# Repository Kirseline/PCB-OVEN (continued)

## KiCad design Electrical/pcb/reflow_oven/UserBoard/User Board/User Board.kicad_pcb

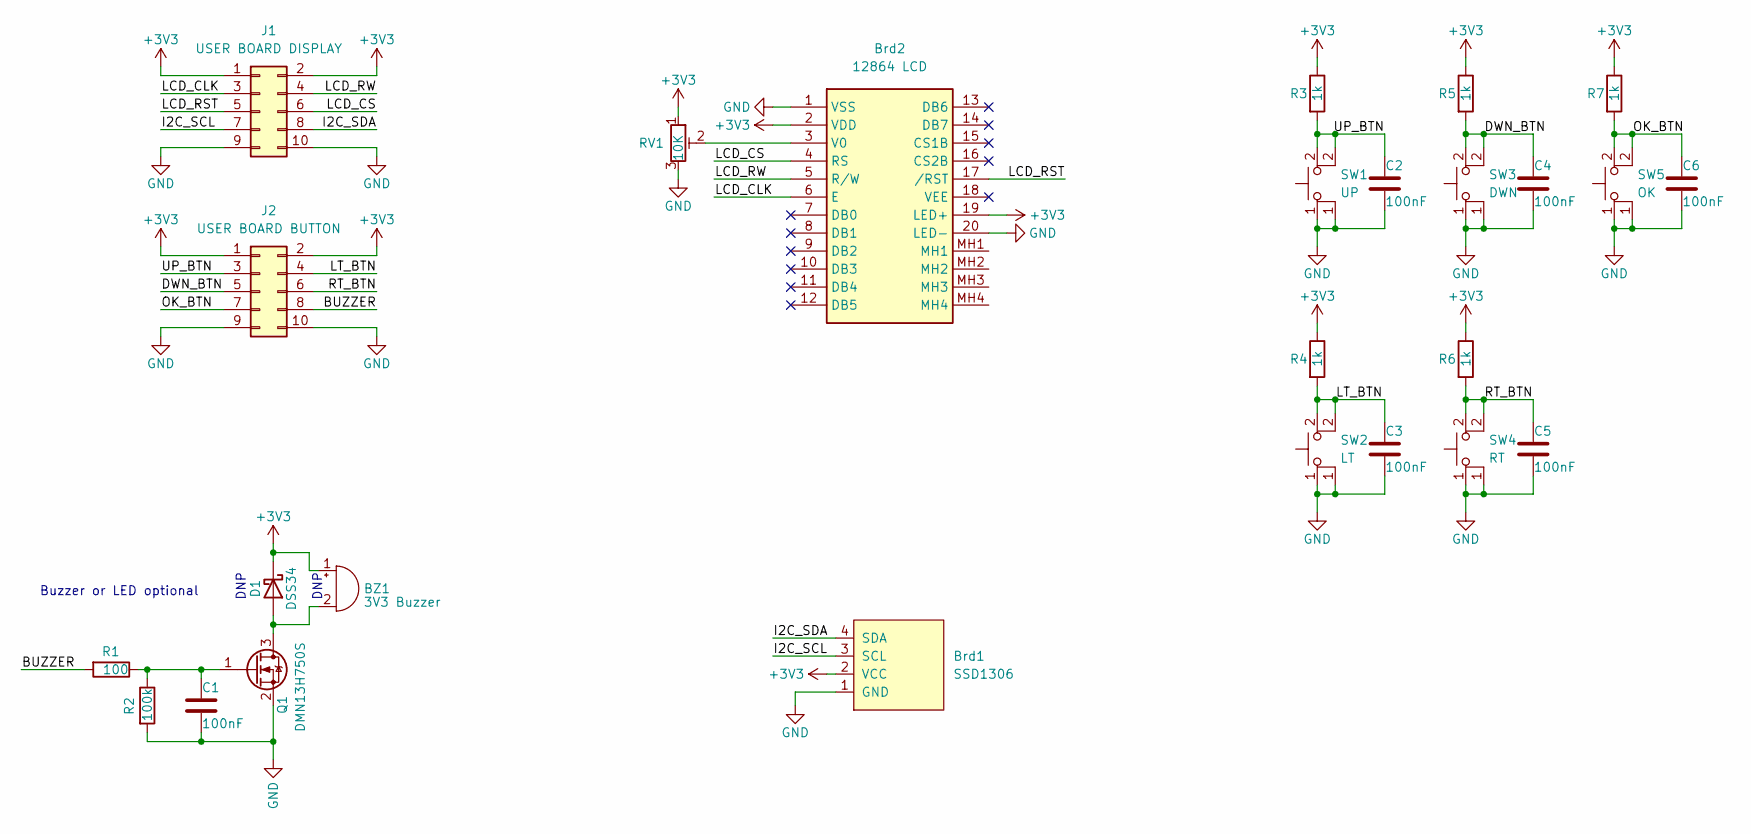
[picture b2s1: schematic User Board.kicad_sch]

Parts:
BZ1: 3V3 Buzzer; MagneticBuzzer_ProSignal_ABT-410-RC
Brd1: SSD1306; 128x64OLED
Brd2: 12864 LCD; NHD12864AZFSWGBWVZ; Manufacturer_Part_Number NHD-12864AZ-FSW-GBW-VZ; Mouser Part Number 763-12864AZ-FSW-GBW
C1, C2, C3, C4, C5, C6: 100nF; C_0603_1608Metric
D1: DSS34; D_SOD-123F
J1: USER BOARD DISPLAY; SHDR10W66P254_2X5_2019X914X986P
J2: USER BOARD BUTTON; SHDR10W66P254_2X5_2019X914X986P
Q1: DMN13H750S; SOT-23
R1: 100; R_0603_1608Metric
R2: 100k; R_0603_1608Metric
R3, R4, R5, R6, R7: 1k; R_0603_1608Metric
RV1: 10K; TC33X2503E
SW1: UP; SW_PUSH_6mm
SW2: LT; SW_PUSH_6mm
SW3: DWN; SW_PUSH_6mm
SW4: RT; SW_PUSH_6mm
SW5: OK; SW_PUSH_6mm

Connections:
+3V3: BZ1.1 (-), Brd1.2 (VCC), Brd2.2 (VDD), Brd2.19 (LED+), D1.1 (K), J1.1, J1.2, J2.1, J2.2, R3.1, R4.1, R5.1, R6.1, R7.1, RV1.1
/BUZZER: J2.8, R1.2
/DWN_BTN: C4.1, J2.5, R5.2, SW3.2
/I2C_SCL: Brd1.3 (SCL), J1.7
/I2C_SDA: Brd1.4 (SDA), J1.8
/LCD_CLK: Brd2.6 (E), J1.3
/LCD_CS: Brd2.4 (RS), J1.6
/LCD_RST: Brd2.17 (/RST), J1.5
/LCD_RW: Brd2.5 (R/W), J1.4
/LT_BTN: C3.1, J2.4, R4.2, SW2.2
/OK_BTN: C6.1, J2.7, R7.2, SW5.2
/RT_BTN: C5.1, J2.6, R6.2, SW4.2
/UP_BTN: C2.1, J2.3, R3.2, SW1.2
GND: Brd1.1 (GND), Brd2.1 (VSS), Brd2.20 (LED-), C1.2, C2.2, C3.2, C4.2, C5.2, C6.2, J1.9, J1.10, J2.9, J2.10, Q1.2 (S), R2.2, RV1.3, SW1.1, SW2.1, SW3.1, SW4.1, SW5.1
unnamed: BZ1.2 (+), D1.2 (A), Q1.3 (D)
unnamed: Brd2.3 (V0), RV1.2
unnamed: C1.1, Q1.1 (G), R1.1, R2.1

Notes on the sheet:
DNP
Buzzer or LED optional

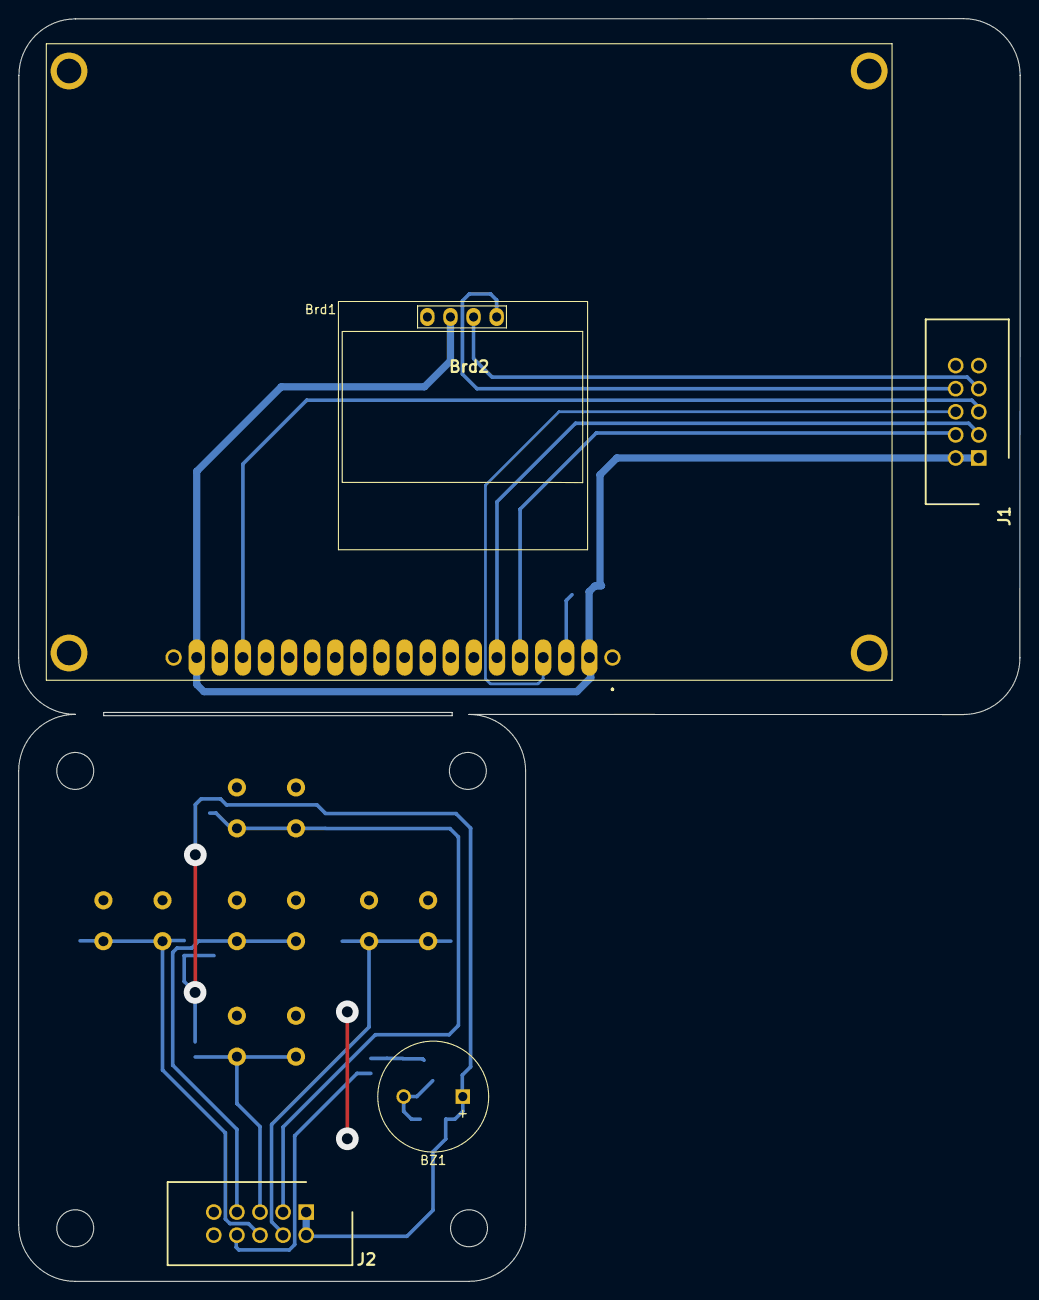
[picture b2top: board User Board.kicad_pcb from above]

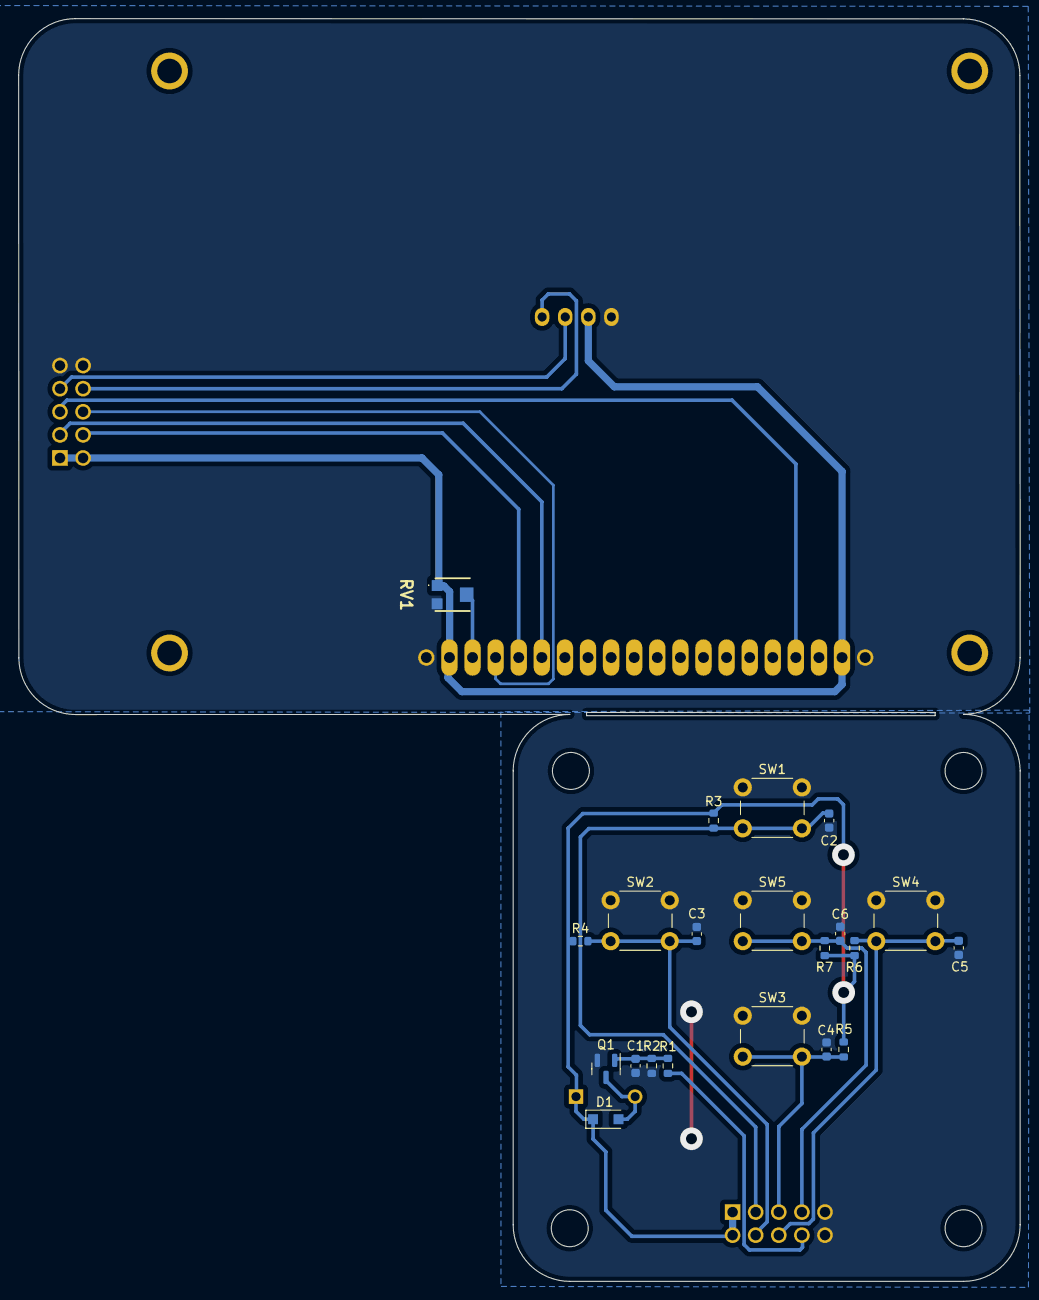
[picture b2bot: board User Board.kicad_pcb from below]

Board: 2 copper layers, 110.1 x 138.9 mm, 26 parts (21 on the bottom side), 17 nets.

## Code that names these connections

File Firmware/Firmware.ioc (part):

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Mcu.Name=STM32F030CCTx
Mcu.Package=LQFP48
Mcu.UserName=STM32F030CCTx
PA0.GPIOParameters=GPIO_Label
PA0.GPIO_Label=VOLTAGE_A
PA0.Mode=IN0
PA0.Signal=ADC_IN0
PA1.GPIOParameters=GPIO_Label
PA1.GPIO_Label=CURRENT_A
PA1.Mode=IN1
PA1.Signal=ADC_IN1
PA10.Mode=Asynchronous
PA10.Signal=USART1_RX
PA11.GPIOParameters=GPIO_Label
PA11.GPIO_Label=CS_A
PA11.Signal=GPIO_Output
PA12.GPIOParameters=GPIO_Label
PA12.GPIO_Label=UP_BTN
PA12.Signal=GPIO_Input
PA13.Mode=Serial_Wire
PA13.Signal=SYS_SWDIO
PA14.Mode=Serial_Wire
PA14.Signal=SYS_SWCLK
PA15.GPIOParameters=GPIO_Label
PA15.GPIO_Label=SSR_A
PA15.Signal=GPIO_Output
PA2.Mode=Asynchronous
PA2.Signal=USART2_TX
PA3.Mode=Asynchronous
PA3.Signal=USART2_RX
PA4.GPIOParameters=GPIO_Label
PA4.GPIO_Label=VOLTAGE_B
PA4.Mode=IN4
PA4.Signal=ADC_IN4
PA5.Mode=Full_Duplex_Master
PA5.Signal=SPI1_SCK
PA6.GPIOParameters=GPIO_Label
PA6.GPIO_Label=CURRENT_B
PA6.Mode=IN6
PA6.Signal=ADC_IN6
PA7.Mode=Full_Duplex_Master
PA7.Signal=SPI1_MOSI
PA8.GPIOParameters=GPIO_Label
PA8.GPIO_Label=CS_B
PA8.Signal=GPIO_Output
PA9.Mode=Asynchronous
PA9.Signal=USART1_TX
PB0.GPIOParameters=GPIO_Label
PB0.GPIO_Label=NTC_A
PB0.Mode=IN8
PB0.Signal=ADC_IN8
PB1.GPIOParameters=GPIO_Label
PB1.GPIO_Label=NTC_B
PB1.Mode=IN9
PB1.Signal=ADC_IN9
PB10.GPIOParameters=GPIO_Label
PB10.GPIO_Label=RT_BTN
PB10.Signal=GPIO_Input
PB11.GPIOParameters=GPIO_Label
PB11.GPIO_Label=LT_BTN
PB11.Signal=GPIO_Input
PB12.GPIOParameters=GPIO_Label
PB12.GPIO_Label=LCD_CS
PB12.Signal=GPIO_Output
PB13.Mode=Simplex_Bidirectional_Master
PB13.Signal=SPI2_SCK
PB14.Signal=GPIO_Output
PB15.Mode=Simplex_Bidirectional_Master
PB15.Signal=SPI2_MOSI
PB2.GPIOParameters=GPIO_Label
PB2.GPIO_Label=OK_BTN
PB2.Signal=GPIO_Input
PB3.GPIOParameters=GPIO_Label
PB3.GPIO_Label=SSR_B
PB3.Signal=GPIO_Output
PB4.Mode=Full_Duplex_Master
PB4.Signal=SPI1_MISO
PB5.GPIOParameters=GPIO_Label
PB5.GPIO_Label=BUZZER
PB5.Signal=S_TIM3_CH2
PB6.Mode=I2C
PB6.Signal=I2C1_SCL
PB7.Mode=I2C
PB7.Signal=I2C1_SDA
PB8.GPIOParameters=GPIO_Label
PB8.GPIO_Label=FAN
PB8.Signal=S_TIM16_CH1
PB9.GPIOParameters=GPIO_Label
PB9.GPIO_Label=DWN_BTN
PB9.Signal=GPIO_Input
PC13.GPIOParameters=GPIO_Label
PC13.GPIO_Label=ZeroCrossing
PC13.Signal=GPIO_Input
PC14OSC32_IN.GPIOParameters=GPIO_Label
PC14OSC32_IN.GPIO_Label=RE_485
PC14OSC32_IN.Signal=GPIO_Output
PC15OSC32_OUT.GPIOParameters=GPIO_Label
PC15OSC32_OUT.GPIO_Label=DE_485
PC15OSC32_OUT.Signal=GPIO_Output
PF0-OSC_IN.Mode=HSE-External-Oscillator
PF0-OSC_IN.Signal=RCC_OSC_IN
PF1-OSC_OUT.Mode=HSE-External-Oscillator
PF1-OSC_OUT.Signal=RCC_OSC_OUT
board=custom

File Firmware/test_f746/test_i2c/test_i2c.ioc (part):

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Mcu.Name=STM32F746ZGTx
Mcu.Package=LQFP144
Mcu.UserName=STM32F746ZGTx
PA1.GPIOParameters=GPIO_Label
PA1.GPIO_Label=RMII_REF_CLK [LAN8742A-CZ-TR_REFCLK0]
PA1.Mode=RMII
PA1.Signal=ETH_REF_CLK
PA10.GPIOParameters=GPIO_Label
PA10.GPIO_Label=USB_ID
PA10.Signal=USB_OTG_FS_ID
PA11.GPIOParameters=GPIO_Label
PA11.GPIO_Label=USB_DM
PA11.Mode=Device_Only
PA11.Signal=USB_OTG_FS_DM
PA12.GPIOParameters=GPIO_Label
PA12.GPIO_Label=USB_DP
PA12.Mode=Device_Only
PA12.Signal=USB_OTG_FS_DP
PA13.GPIOParameters=GPIO_Label
PA13.GPIO_Label=TMS
PA13.Mode=Serial_Wire
PA13.Signal=SYS_JTMS-SWDIO
PA14.GPIOParameters=GPIO_Label
PA14.GPIO_Label=TCK
PA14.Mode=Serial_Wire
PA14.Signal=SYS_JTCK-SWCLK
PA2.GPIOParameters=GPIO_Label
PA2.GPIO_Label=RMII_MDIO [LAN8742A-CZ-TR_MDIO]
PA2.Mode=RMII
PA2.Signal=ETH_MDIO
PA7.GPIOParameters=GPIO_Label
PA7.GPIO_Label=RMII_CRS_DV [LAN8742A-CZ-TR_CRS_DV]
PA7.Mode=RMII
PA7.Signal=ETH_CRS_DV
PA8.GPIOParameters=GPIO_Label
PA8.GPIO_Label=USB_SOF [TP1]
PA8.Mode=Activate_SOF_FS
PA8.Signal=USB_OTG_FS_SOF
PA9.GPIOParameters=GPIO_Label
PA9.GPIO_Label=USB_VBUS
PA9.Mode=Activate_VBUS
PA9.Signal=USB_OTG_FS_VBUS
PB0.GPIOParameters=GPIO_Label
PB0.GPIO_Label=LD1 [Green]
PB0.Signal=GPIO_Output
PB13.GPIOParameters=GPIO_Label
PB13.GPIO_Label=RMII_TXD1 [LAN8742A-CZ-TR_TXD1]
PB13.Mode=RMII
PB13.Signal=ETH_TXD1
PB14.GPIOParameters=GPIO_Label
PB14.GPIO_Label=LD3 [Red]
PB14.Signal=GPIO_Output
PB3.GPIOParameters=GPIO_Label
PB3.GPIO_Label=SW0
PB3.Signal=SYS_JTDO-SWO
PB7.GPIOParameters=GPIO_Label
PB7.GPIO_Label=LD2 [Blue]
PB7.Signal=GPIO_Output
PB8.Mode=I2C
PB8.Signal=I2C1_SCL
PB9.Mode=I2C
PB9.Signal=I2C1_SDA
PC1.GPIOParameters=GPIO_Label
PC1.GPIO_Label=RMII_MDC [LAN8742A-CZ-TR_MDC]
PC1.Mode=RMII
PC1.Signal=ETH_MDC
PC13.GPIOParameters=GPIO_Label
PC13.GPIO_Label=USER_Btn [B1]
PC13.Signal=GPXTI13
PC14/OSC32_IN.Mode=LSE-External-Oscillator
PC14/OSC32_IN.Signal=RCC_OSC32_IN
PC15/OSC32_OUT.Mode=LSE-External-Oscillator
PC15/OSC32_OUT.Signal=RCC_OSC32_OUT
PC4.GPIOParameters=GPIO_Label
PC4.GPIO_Label=RMII_RXD0 [LAN8742A-CZ-TR_RXD0]
PC4.Mode=RMII
PC4.Signal=ETH_RXD0
PC5.GPIOParameters=GPIO_Label
PC5.GPIO_Label=RMII_RXD1 [LAN8742A-CZ-TR_RXD1]
PC5.Mode=RMII
PC5.Signal=ETH_RXD1
PD8.GPIOParameters=GPIO_PuPd,GPIO_Label
PD8.GPIO_Label=STLK_RX [STM32F103CBT6_PA3]
PD8.GPIO_PuPd=GPIO_PULLUP
PD8.Mode=Asynchronous
PD8.Signal=USART3_TX
PD9.GPIOParameters=GPIO_PuPd,GPIO_Label
PD9.GPIO_Label=STLK_TX [STM32F103CBT6_PA2]
PD9.GPIO_PuPd=GPIO_PULLUP
PD9.Mode=Asynchronous
PD9.Signal=USART3_RX
PG11.GPIOParameters=GPIO_Label
PG11.GPIO_Label=RMII_TX_EN [LAN8742A-CZ-TR_TXEN]
PG11.Mode=RMII
PG11.Signal=ETH_TX_EN
PG13.GPIOParameters=GPIO_Label
PG13.GPIO_Label=RMII_TXD0 [LAN8742A-CZ-TR_TXD0]
PG13.Mode=RMII
PG13.Signal=ETH_TXD0
PG6.GPIOParameters=GPIO_Label
PG6.GPIO_Label=USB_PowerSwitchOn [STMPS2151STR_EN]
PG6.Signal=GPIO_Output
PG7.GPIOParameters=GPIO_Label
PG7.GPIO_Label=USB_OverCurrent [STMPS2151STR_FAULT]
PG7.Signal=GPIO_Input
PH0/OSC_IN.GPIOParameters=GPIO_Label
PH0/OSC_IN.GPIO_Label=MCO [STM32F103CBT6_PA8]
PH0/OSC_IN.Mode=HSE-External-Clock-Source
PH0/OSC_IN.Signal=RCC_OSC_IN
PH1/OSC_OUT.Mode=HSE-External-Clock-Source
PH1/OSC_OUT.Signal=RCC_OSC_OUT
RCC.HSE_VALUE=8000000
RCC.SYSCLKFreq_VALUE=72000000
RCC.SYSCLKSource=RCC_SYSCLKSOURCE_PLLCLK
RCC.SYSCLKSourceVirtual=RCC_SYSCLKSOURCE_PLLCLK
board=NUCLEO-F746ZG
boardIOC=true

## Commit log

2023-07-31 power stage
    schematic of power stage done
2023-08-04 schematic
    added microcontrroller and .ioc file
    added usb serial converter
2023-08-05 interface
    partial interface schematic
2023-08-07 analog Sensing
    -voltage and current sensor
    -zero crossing
    -temperature
2023-08-08 schematic
    -interface
    -micro
    todo
    output
    routing
2023-08-11 functionality
    done output stage
2023-08-11 pcb layout
    initial pcb layout
2023-08-14 addon
    - ferrites application notes
2023-08-22 pcb layout
2023-08-23 production candidate
    finished routing
2023-08-24 fab out
    added fabrication output
2023-08-24 new board
    user input board
    note: can be etched at home
2023-08-25 fix
    changed display footprint
2023-08-26 addon
    documentation pics
    adjust oshw logo
2023-09-01 addon
    test nucleo f746
2023-09-06 documentazione
    aggiunta documentazione
2023-09-06 tesi
2023-09-07 user board
    user board fab file
2023-09-07 documentazione
    modifiche tesi
2023-09-08 peripheral initial test
    tested i2c ok
    tested max6675 ok
    ssr ok
2023-09-13 test
